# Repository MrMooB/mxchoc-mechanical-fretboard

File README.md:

# mxchoc-mechanical-fretboard
A fretboard for Cherry MX/Kailh Choc mechanical switches with two different LED's support

This is Crafty's remake of his fretboard (https://github.com/Crafty-The-Fox/GH-Mechfret-Kailh-Choc-mini) to fit for new Kail Choc and Cherry MX type switches.
Should fit most if not all guitars (untested yet). May need small adjustments to holes.
Supports both 5050 and 2020 SMD LED's

For WoR guitars:
You will need to cut the end of the board as it is too long.
You will also need to cut a bit on the sides as it is too wide at the end. Or you can remove some plastic from the guitar.

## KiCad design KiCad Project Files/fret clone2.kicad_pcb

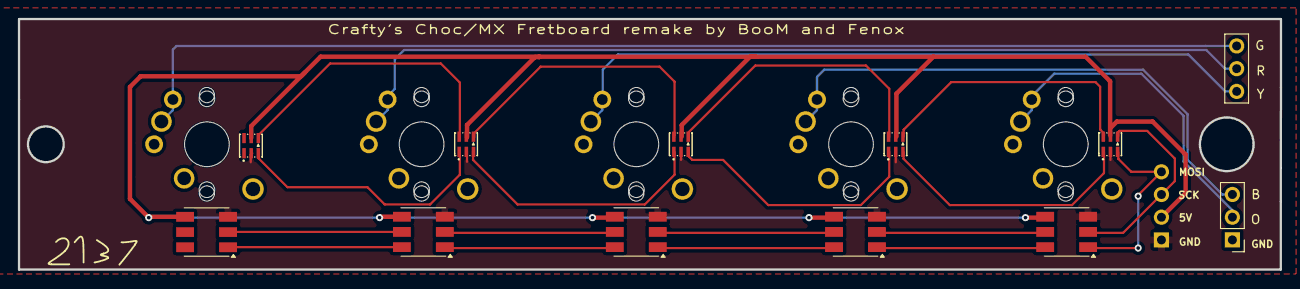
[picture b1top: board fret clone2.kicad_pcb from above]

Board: 2 copper layers, 141.1 x 28.0 mm, 18 parts (0 on the bottom side), 26 nets.

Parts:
CH6, CH7, CH8, CH9, CH10: choc_v1_SW_solder; SW_choc_v1+v2+mx_1u
D2, D3, D4, D5, D6: APA102; LED_RGB_5050-6
J1, J2: Conn_01x03_Pin; PinHeader_1x03_P2.54mm_Vertical
J3: Conn_01x04_Pin; PinHeader_1x04_P2.54mm_Vertical
LED1, LED2, LED3, LED4, LED5: SK9822-EC20

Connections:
/CKI: D6.2 (CI), J3.2, LED1.4 (CKI)
/SDI: D6.1 (DI), J3.1, LED1.3 (SDI)
GND: D2.3 (GND), D3.3 (GND), D4.3 (GND), D5.3 (GND), D6.3 (GND), J3.4, LED1.2 (GND), LED2.2 (GND), LED3.2 (GND), LED4.2 (GND), LED5.2 (GND)
unnamed: D2.2 (CI), D3.5 (CO)
unnamed: D2.1 (DI), D3.6 (DO)
unnamed: D3.2 (CI), D4.5 (CO)
unnamed: D3.1 (DI), D4.6 (DO)
unnamed: D4.2 (CI), D5.5 (CO)
unnamed: D4.1 (DI), D5.6 (DO)
unnamed: D5.2 (CI), D6.5 (CO)
unnamed: D5.1 (DI), D6.6 (DO)
unnamed: CH6.2, CH7.2, CH8.2, CH9.2, CH10.2, J1.1
unnamed: CH10.1, J1.2
unnamed: CH9.1, J1.3
unnamed: CH8.1, J2.1
unnamed: CH7.1, J2.2
unnamed: CH6.1, J2.3
unnamed: LED1.6 (CKO), LED2.4 (CKI)
unnamed: LED1.1 (SDO), LED2.3 (SDI)
unnamed: LED2.6 (CKO), LED3.4 (CKI)
unnamed: LED2.1 (SDO), LED3.3 (SDI)
unnamed: LED3.6 (CKO), LED4.4 (CKI)
unnamed: LED3.1 (SDO), LED4.3 (SDI)
unnamed: LED4.6 (CKO), LED5.4 (CKI)
unnamed: LED4.1 (SDO), LED5.3 (SDI)
VCC: D2.4 (VCC), D3.4 (VCC), D4.4 (VCC), D5.4 (VCC), D6.4 (VCC), J3.3, LED1.5 (VDD), LED2.5 (VDD), LED3.5 (VDD), LED4.5 (VDD), LED5.5 (VDD)
